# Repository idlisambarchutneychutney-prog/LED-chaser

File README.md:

# LED-chaser

A custom printed circuit board designed to act as an animated backlight for a 3D-printed statue of Lord Shiva. The circuit uses a 555 timer to generate a clock pulse and a CD4017 decade counter to create a chasing LED sequence.

# Overview & Design Process
This project was designed in KiCad over the course of about 4 hours. While I used the [Hack Club Blinky Blueprint](https://blueprint.hackclub.com/starter-projects/blinky) as a foundational reference for the circuit logic, the physical board layout and form factor are entirely custom. 

# Hardware & 3D Integration
I built this specific PCB layout to serve as a custom lighting fixture for a 100mm x 100mm 3D-printed statue. The PCB dimensions were strictly constrained to remain completely hidden behind the print. 

To achieve a glowing halo effect:
* The 5mm LED footprints are routed in an inverted "U" shape along the perimeter of the board.
* The LEDs will be reverse-mounted on the back of the PCB. 
* When powered, the chasing sequence will smoothly frame the statue from behind.

# Bill of Materials (BOM)
https://docs.google.com/spreadsheets/d/1dknvj6RsMCPzlCs72U_A4Biw2XVm9xkfnfsrWRNoysQ/edit?usp=sharing

## Manufacturing
To manufacture this board, download `gerber.zip` from the root directory and upload it to a fab house like JLCPCB. The board is designed with standard 2-layer specifications and fits within a 100x100mm footprint.

## License
This project is completely open source under the MIT License.

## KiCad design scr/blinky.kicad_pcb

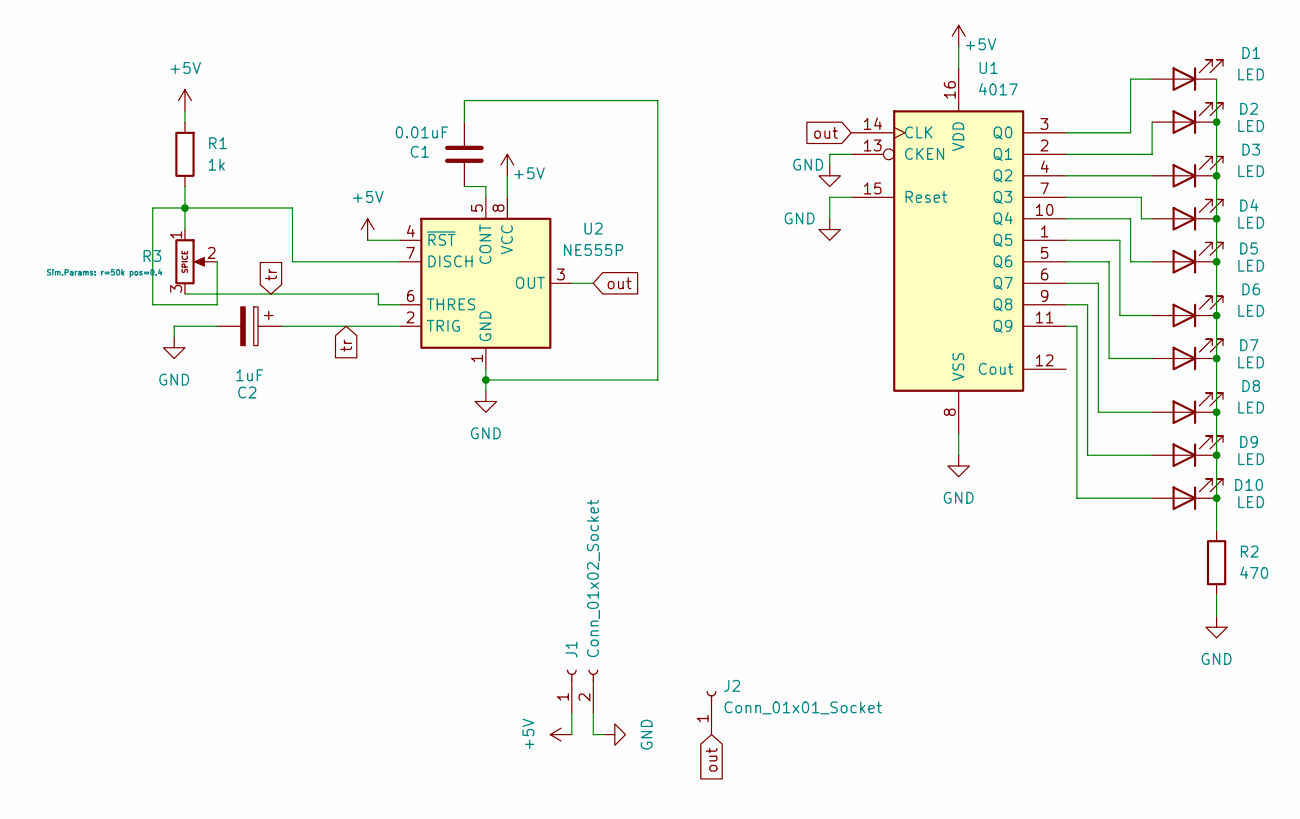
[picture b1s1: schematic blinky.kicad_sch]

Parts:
C1: 0.01uF; C_Disc_D7.5mm_W2.5mm_P5.00mm
C2: 1uF; CP_Radial_D5.0mm_P2.00mm
D1, D2, D3, D4, D5, D6, D7, D8, D9, D10: LED; LED_D3.0mm
J1: Conn_01x02_Socket; PinHeader_1x02_P2.54mm_Vertical
J2: Conn_01x01_Socket; PinHeader_1x01_P2.54mm_Vertical
R1: 1k; R_Axial_DIN0207_L6.3mm_D2.5mm_P7.62mm_Horizontal
R2: 470; R_Axial_DIN0207_L6.3mm_D2.5mm_P7.62mm_Horizontal
R3: Potentiometer; Potentiometer_Vishay_T93YA_Vertical
U1: 4017; N16
U2: NE555P; DIP-8_W7.62mm

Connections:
+5V: J1.1, R1.2, U1.16 (VDD), U2.4 (~RST), U2.8 (VCC)
GND: C1.1, C2.2, J1.2, R2.2, U1.8 (VSS), U1.13 (CKEN), U1.15 (Reset), U2.1 (GND)
unnamed: D1.2 (A), U1.3 (Q0)
unnamed: D1.1 (K), D2.1 (K), D3.1 (K), D4.1 (K), D5.1 (K), D6.1 (K), D7.1 (K), D8.1 (K), D9.1 (K), D10.1 (K), R2.1
unnamed: D2.2 (A), U1.2 (Q1)
unnamed: D3.2 (A), U1.4 (Q2)
unnamed: D4.2 (A), U1.7 (Q3)
unnamed: D5.2 (A), U1.10 (Q4)
unnamed: D6.2 (A), U1.1 (Q5)
unnamed: D7.2 (A), U1.5 (Q6)
unnamed: D8.2 (A), U1.6 (Q7)
unnamed: D9.2 (A), U1.9 (Q8)
unnamed: D10.2 (A), U1.11 (Q9)
unnamed: C1.2, U2.5 (CONT)
unnamed: R1.1, R3.1, R3.2, U2.7 (DISCH)
out: J2.1 (Pin_1_1), U1.14 (CLK), U2.3 (OUT)
tr: C2.1, R3.3, U2.2 (TRIG), U2.6 (THRES)

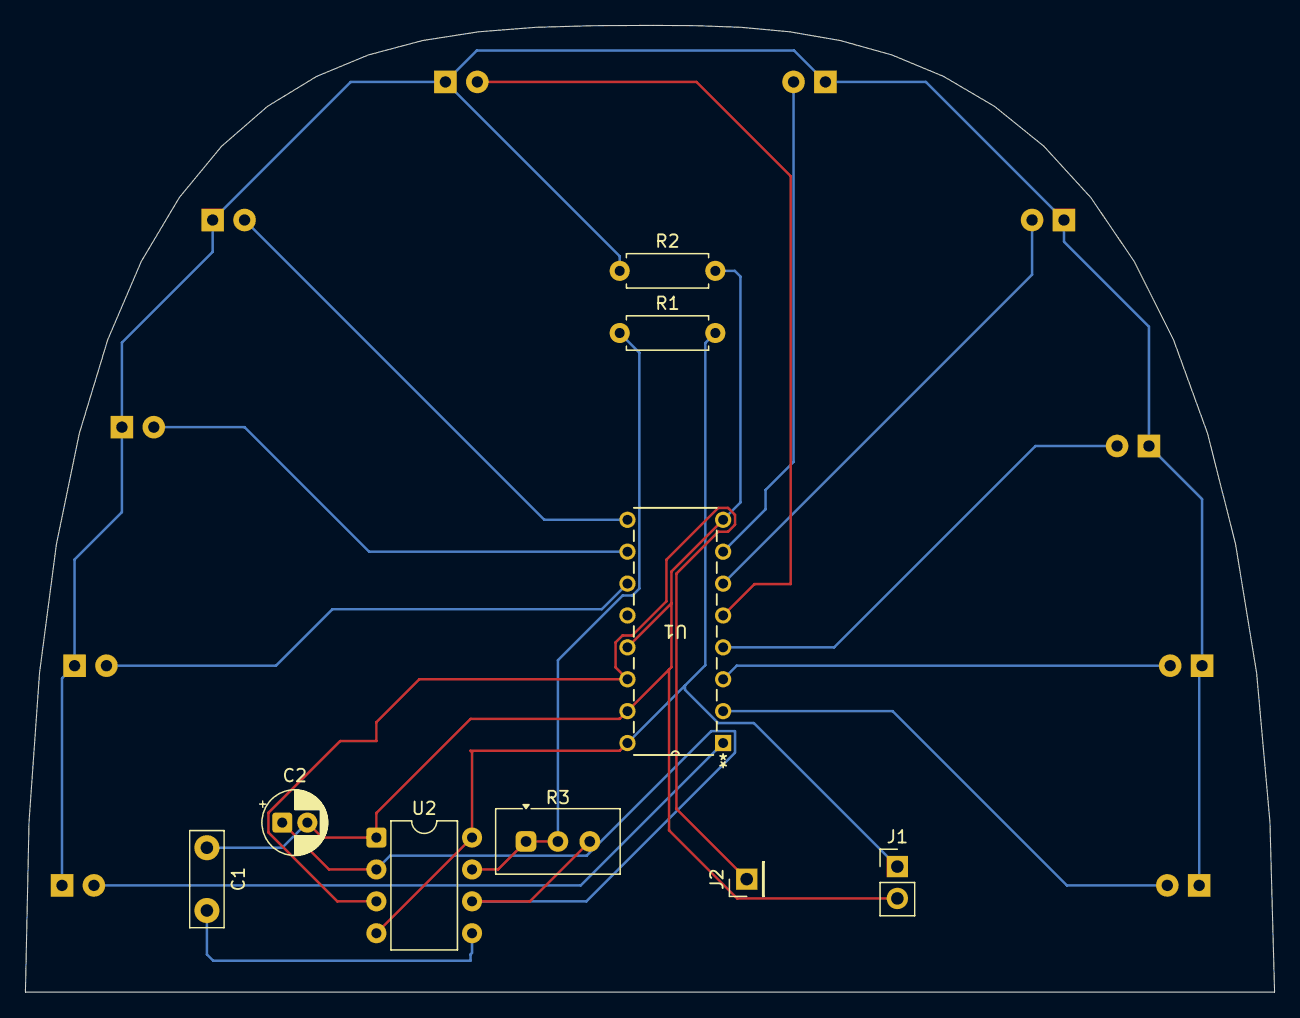
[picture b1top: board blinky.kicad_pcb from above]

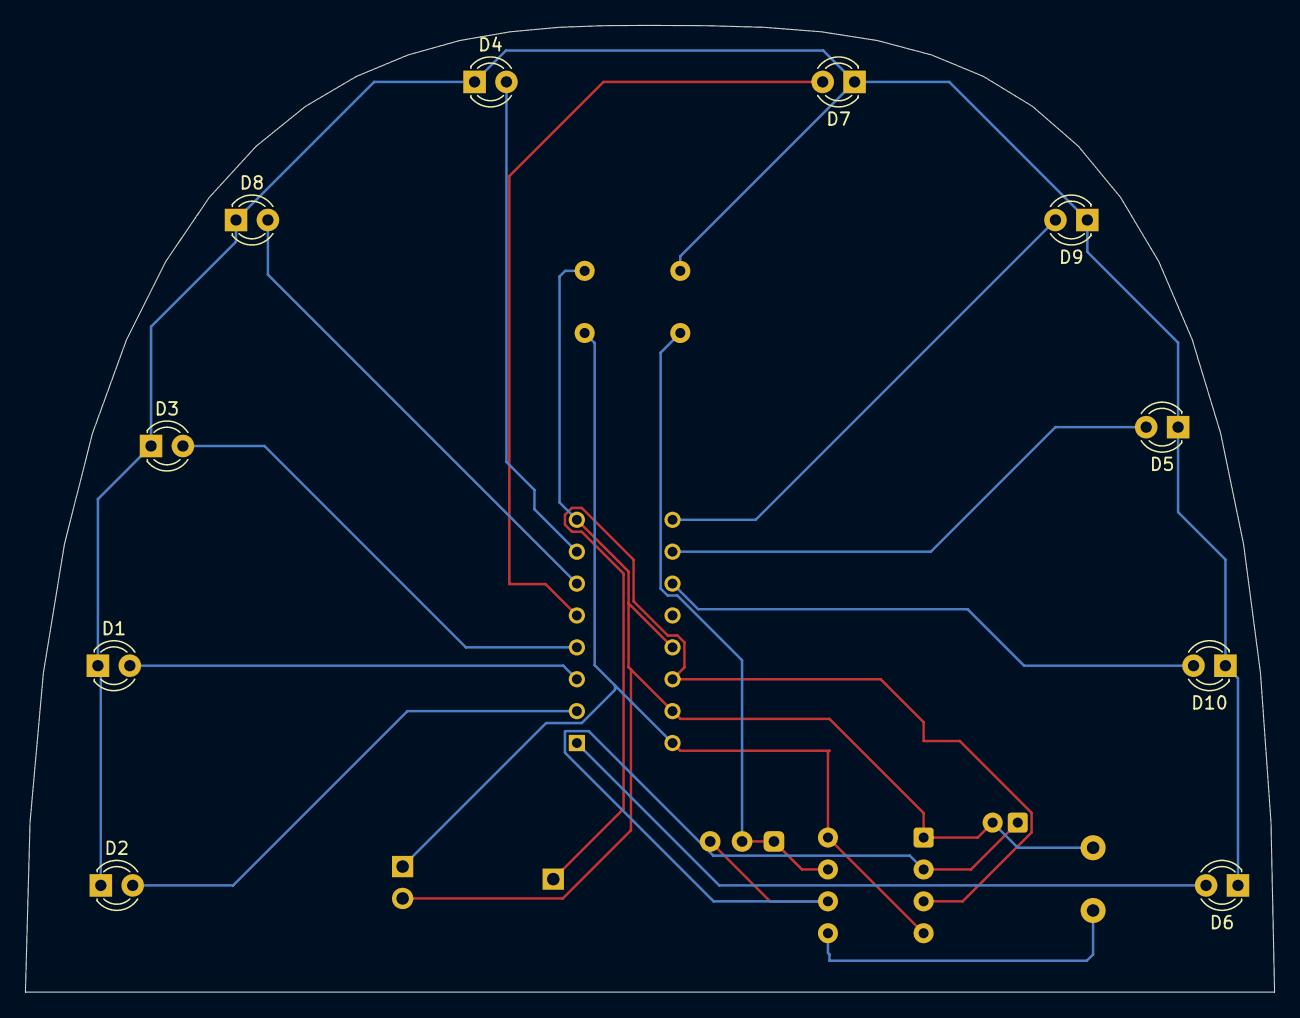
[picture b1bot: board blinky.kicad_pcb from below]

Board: 2 copper layers, 99.5 x 77.0 mm, 19 parts (10 on the bottom side), 17 nets.
